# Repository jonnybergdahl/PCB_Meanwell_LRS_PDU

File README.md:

# PDU_Meanwell_LRS

This is a project for a simple PDU (Power Distribution Unit) using Meanwell LRS-x-y power supplies.

It is using XT60 connectors for power, and car fuse holders for protection.

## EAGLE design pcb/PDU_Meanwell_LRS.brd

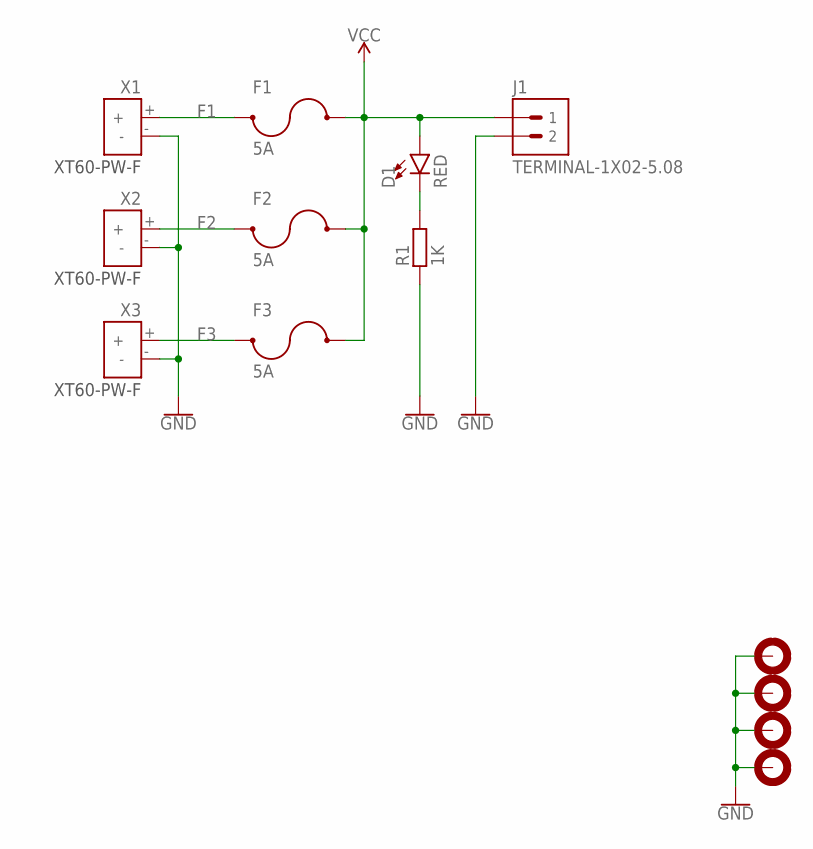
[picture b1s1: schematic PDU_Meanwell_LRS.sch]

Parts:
D1: RED; LED5MM
F1, F2, F3: 5A; CAR-FUSE-MEDIUM
H1, H2, H3, H4: MOUNTHOLE-PAD3.2; 3.2-PAD
J1: TERMINAL-1X02-5.08; TERMINAL-5.08-2P
R1: 1K; R0603
X1, X2, X3: XT60-PW-F

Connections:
F1: F1.1@1 (1), F1.1@2 (1), X1.+
F2: F2.1@1 (1), F2.1@2 (1), X2.+
F3: F3.1@1 (1), F3.1@2 (1), X3.+
GND: H1.B3,2, H2.B3,2, H3.B3,2, H4.B3,2, J1.P$2 (2), R1.1, X1.-, X2.-, X3.-
unnamed: D1.K (C), R1.2
VCC: D1.A, F1.2@3 (2), F1.2@4 (2), F2.2@3 (2), F2.2@4 (2), F3.2@3 (2), F3.2@4 (2), J1.P$1 (1)

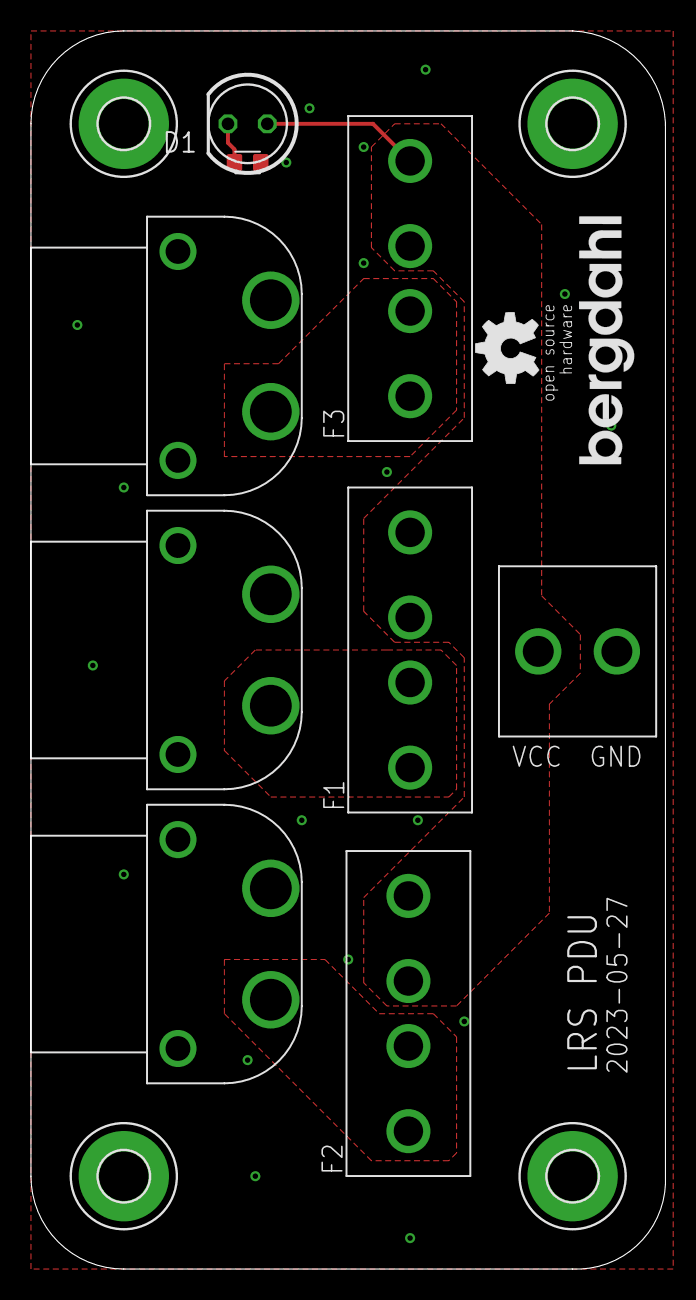
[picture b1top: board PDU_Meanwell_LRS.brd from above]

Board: 2 copper layers, 41.0 x 80.0 mm, 17 parts (0 on the bottom side), 6 nets.

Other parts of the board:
U$1: BERGDAHL-20MM-TPLACE
U$2: OSHW-5MM-TPLACE
U$3: BERGDAHL-20MM-BPLACE
U$4: OSHW-8MM-BPLACE

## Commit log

2023-05-27 Add PDF
